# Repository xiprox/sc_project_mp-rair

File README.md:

2013 School & International IT Project.

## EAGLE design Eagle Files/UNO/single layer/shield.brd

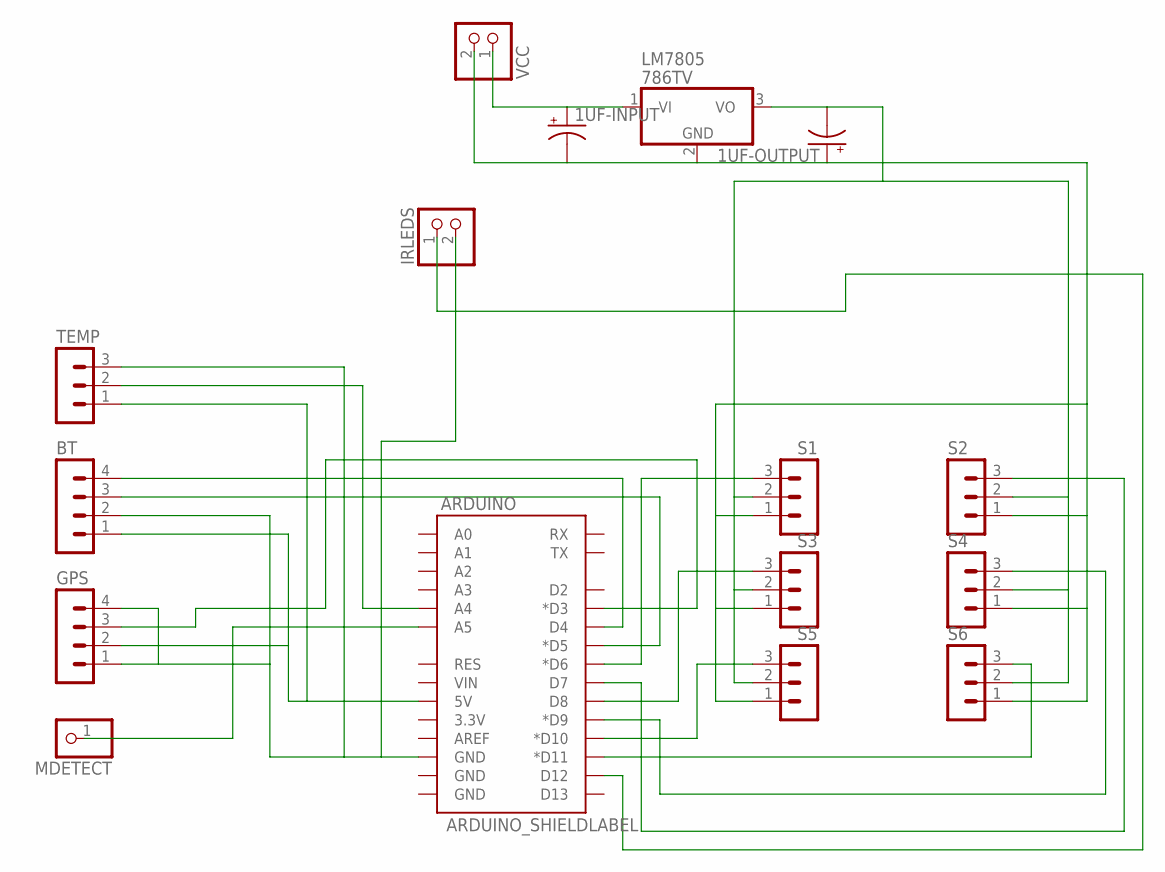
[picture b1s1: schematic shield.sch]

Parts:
1UF-INPUT, 1UF-OUTPUT: CAP_POLPTH4; CPOL-RADIAL-1000UF-25V
ARDUINO: ARDUINO_SHIELDLABEL; DUEMILANOVE_SHIELD
BT: MA04-1
GPS: MA04-1
IRLEDS: PINHD-1X2; 1X02
LM7805: 786TV; TO220V
MDETECT: PINHD-1X1; 1X01
S1, S2, S3, S4, S5, S6: MA03-1
TEMP: MA03-1
VCC: PINHD-1X2; 1X02

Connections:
MDETECT: ARDUINO.A5, MDETECT.1
unnamed: ARDUINO.D12, IRLEDS.1
unnamed: ARDUINO.D6 (*D6), S1.3
unnamed: ARDUINO.D7, S2.3
unnamed: ARDUINO.D8, S3.3
unnamed: ARDUINO.D9 (*D9), S4.3
unnamed: ARDUINO.D10 (*D10), S5.3
unnamed: ARDUINO.D11 (*D11), S6.3
unnamed: ARDUINO.5V, BT.1, GPS.2, TEMP.1
unnamed: ARDUINO.GND@2 (GND), BT.2, GPS.1, GPS.4, IRLEDS.2, TEMP.3
unnamed: ARDUINO.D5 (*D5), BT.3
unnamed: ARDUINO.D4, BT.4
unnamed: ARDUINO.D3 (*D3), GPS.3
unnamed: ARDUINO.A4, TEMP.2
unnamed: 1UF-INPUT.1 (+), LM7805.1 (VI), VCC.1
unnamed: 1UF-INPUT.2 (-), 1UF-OUTPUT.1 (+), LM7805.2 (GND), S1.1, S2.1, S3.1, S4.1, S5.1, S6.1, VCC.2
unnamed: 1UF-OUTPUT.2 (-), LM7805.3 (VO), S1.2, S2.2, S3.2, S4.2, S5.2, S6.2

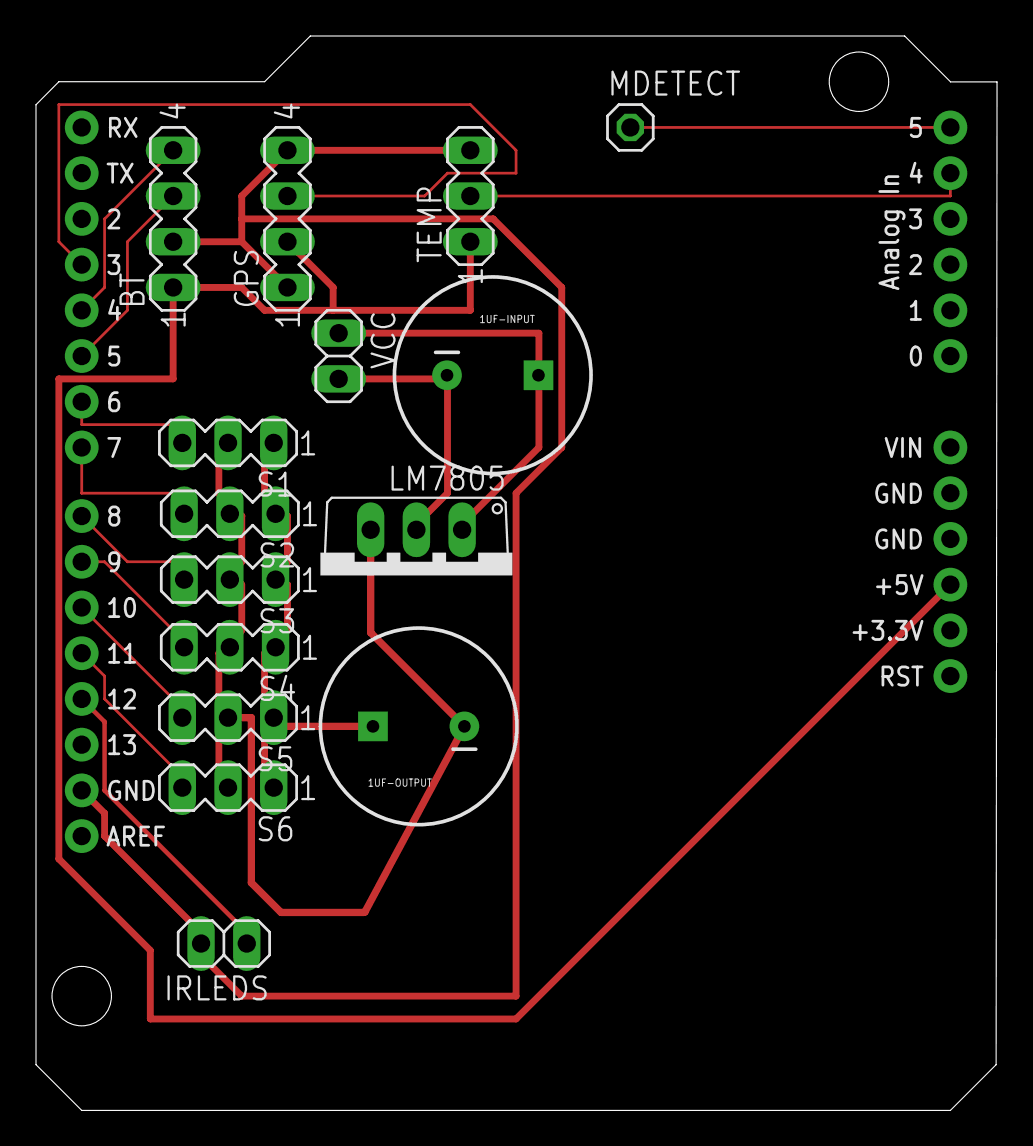
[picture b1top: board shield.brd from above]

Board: 2 copper layers, 53.4 x 59.7 mm, 16 parts (0 on the bottom side), 17 nets.

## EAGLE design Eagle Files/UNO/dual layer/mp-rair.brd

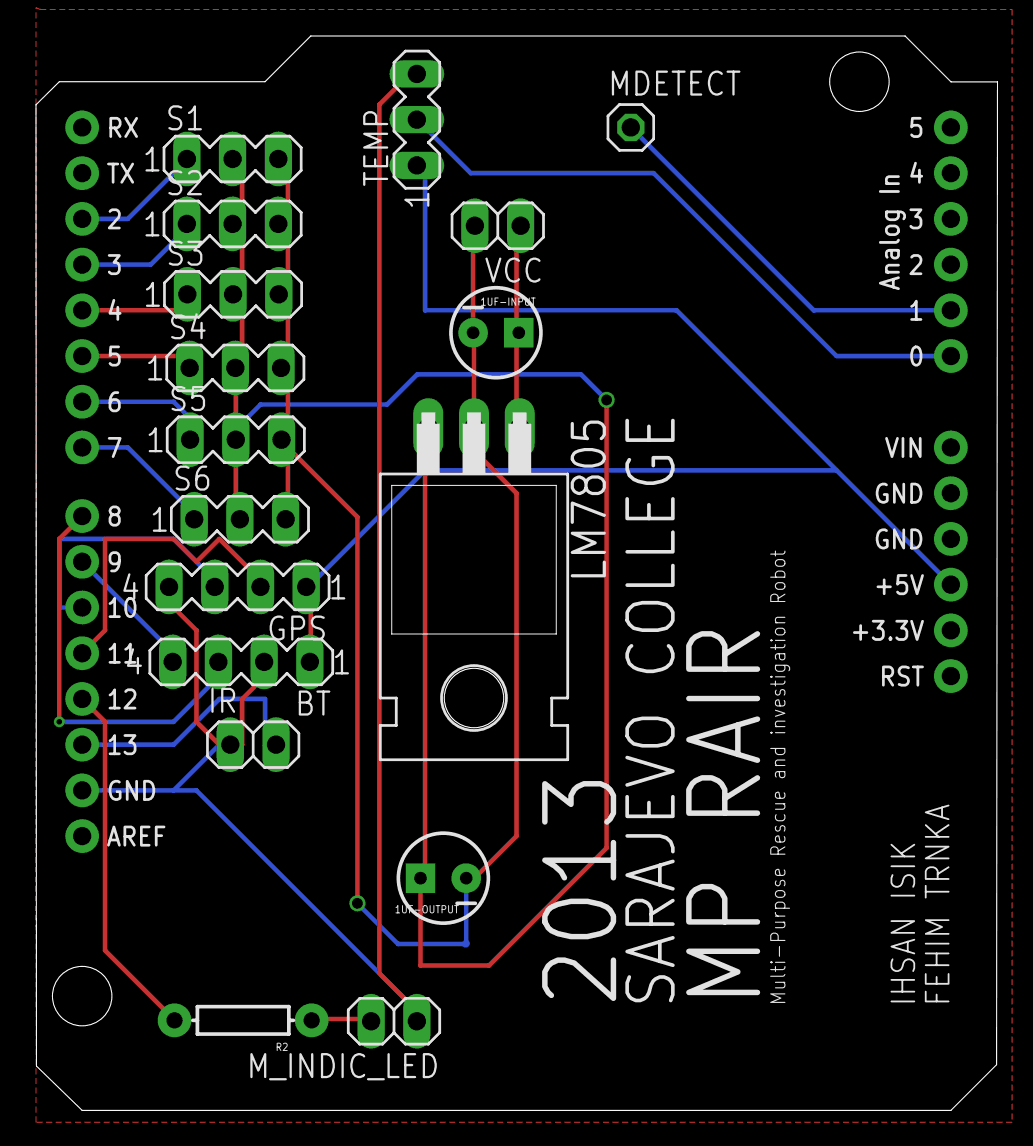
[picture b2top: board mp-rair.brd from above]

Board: 2 copper layers, 53.4 x 59.7 mm, 18 parts (0 on the bottom side), 20 nets.

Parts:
1UF-INPUT, 1UF-OUTPUT: CPOL-RADIAL-10UF-25V
ARDUINO: ARDUINO_SHIELDLABEL; DUEMILANOVE_SHIELD
BT: MA04-1
GPS: MA04-1
IR: 1X02
LM7805: TO220H
MDETECT: 1X01
M_INDIC_LED: 1X02
R2: AXIAL-0.3
S1, S2, S3, S4, S5, S6: MA03-1
TEMP: MA03-1
VCC: 1X02

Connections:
unnamed: ARDUINO.D2, S1.1
unnamed: ARDUINO.5V, BT.1, GPS.1, TEMP.1
unnamed: ARDUINO.GND@2, BT.2, GPS.4, IR.1, M_INDIC_LED.1, TEMP.3
unnamed: ARDUINO.D3, S2.1
unnamed: ARDUINO.D4, S3.1
unnamed: ARDUINO.D5, S4.1
unnamed: ARDUINO.D6, S5.1
unnamed: ARDUINO.D7, S6.1
unnamed: 1UF-INPUT.2, 1UF-OUTPUT.2, LM7805.2, S1.3, S2.3, S3.3, S4.3, S5.3, S6.3, VCC.2
unnamed: 1UF-OUTPUT.1, LM7805.3, S1.2, S2.2, S3.2, S4.2, S5.2, S6.2
unnamed: ARDUINO.A0, TEMP.2
unnamed: ARDUINO.D8, BT.3
unnamed: ARDUINO.D9, BT.4
unnamed: M_INDIC_LED.2, R2.P$1
unnamed: 1UF-INPUT.1, LM7805.1, VCC.1
unnamed: ARDUINO.D12, R2.P$2
unnamed: ARDUINO.D11, GPS.2
unnamed: ARDUINO.D13, IR.2
unnamed: ARDUINO.D10, GPS.3
unnamed: ARDUINO.A1, MDETECT.1

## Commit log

2013-02-16 recreated whole repo
2013-05-01 pushed unfinished presentation
2013-05-01 pushed unfinished pptx presentation
2013-05-03 updates on presentation and pushed references
2013-05-04 updates on pptx
2013-05-12 pptx updates and pushed schematic
2013-05-13 Pushed board image and pptx updates
2013-05-13 bunch of additions
    Completed Presentation, bunch of new logos, T-Shirt design, pictures,
    and moved schematics and board pictures.
2013-05-14 Moved windows app into a new repo
2013-05-15 final changes in presentation + bt module img

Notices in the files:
parts and their libraries:
SparkFun-Boards: Licensing: CC v3.0 Share-Alike You are welcome to use this library for commercial purposes.
